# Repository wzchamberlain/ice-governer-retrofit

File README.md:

# ICE-Governor-Retrofit

## Rationale & Goal

The goal of this project is to provide a low cost electronic governor retrofit for small/carburetor engines to replace poor, worn, malfunctioning, or destroyed governors. Typical off-the-shelf variants cost in excess of $100 USD, surpassing the remaining value of the small engine they might be applied to. The target deployment engine this project is built for specifically is a 4000W single phase (true) generator, where the engine must be kept at a steady 3600 RPM or 3000 RPM for 60 Hz or 50 Hz respectively. Provisions should be made in the design to allow for dynamic target speed setting both for fine tuning or for a dynamic governor, such as in a small tractor or ride on lawnmower, perhaps even a gas powertool.

## Pin Count

### Pin Planning
Max IO: 6 pins. One of the potentiometers should be limited to range of 2.5V to HIGH so that I can be used on the RESET line of the ATTiny (GROUND/LOW Pull is reset active).
1. Spark Detect +
    - Bit 2 (Pin7) is the external interrupt pin and would be preferred, however there is only one external interrupt.
2. Spark Detect -
    - Bit 0 (Pin 5) for convince, has Pin Change Interrupt.
3. Servo PWM
    - Bit 4 or Bit 1 should be used for the non-inverted PWM output.
    - Pin 6 or Pin 3.
4. Speed (Position) Potentiometer
    - Potentiometer for speed
    - (Optional) Grounding/High switch to signal off.
        - Cannot be on reset (Bit 5, Pin 1)
5. Integral Potentiometer
6. Derivative Potentiometer

### Signaled Shutoff Plan
This variant of the schematic and pin planning uses the switch (SPDT) to signal the ATTiny to ramp down (and stall) the engine before entering a sleep state. This will result in a parasitic draw when in sleep/off to allow the microcontroller to wake up and for the LDO Voltage Regulator to down-regulate the battery. This is done as a trade off to make operation safer by ensuring that the throttle body is closed to prevent a runaway. The battery planned is a relatively larger 9V box battery.

#### By Pin Number
1. Second Order Reaction
2. First Order Reaction
3. Speed Set and Sleep Trigger
4. GND
5. Spark Trigger
6. Servo Position PWM
7. Spark Trigger
8. VCC

#### By Port Number (All Port B)
0. Spark Trigger
1. Servo Position PWM
2. Spark Trigger
3. First Order Reaction
4. Speed Set and Sleep Trigger
5. Second Order Reaction

#### Schematic Plan

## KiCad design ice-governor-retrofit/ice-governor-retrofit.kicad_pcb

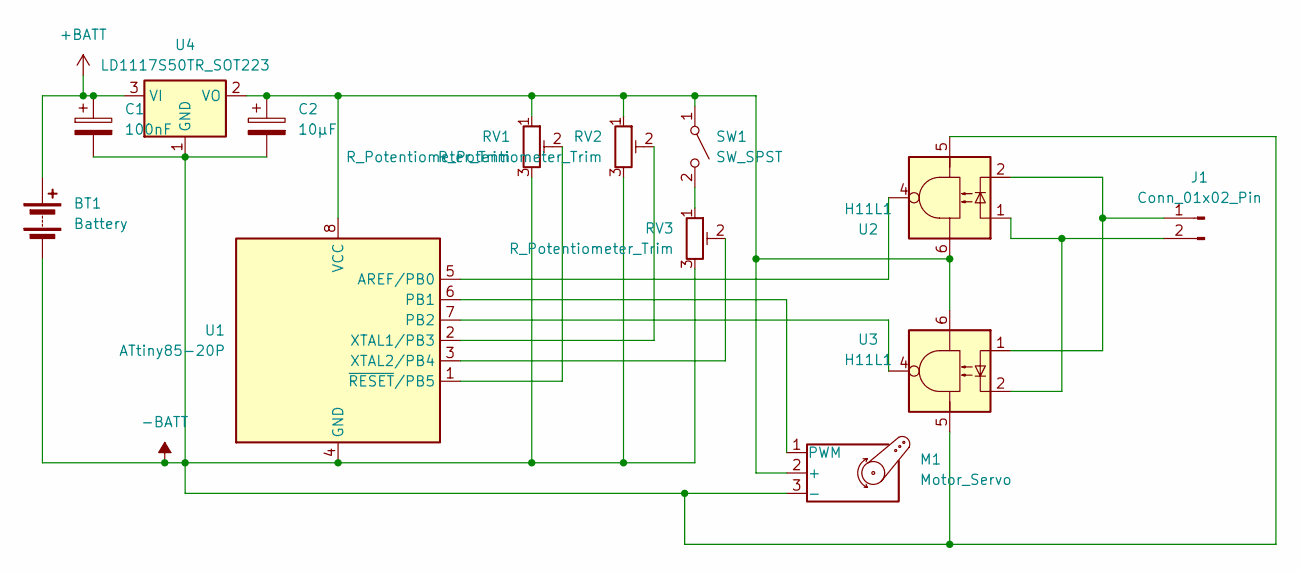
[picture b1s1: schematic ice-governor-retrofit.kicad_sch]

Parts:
BT1: Battery; BatteryHolder_Eagle_12BH611-GR
C1: 100nF; CP_Radial_D5.0mm_P2.50mm
C2: 10μF; CP_Radial_D5.0mm_P2.50mm
J1: Conn_01x02_Pin; PinHeader_1x02_P2.54mm_Vertical
M1: Motor_Servo; PinHeader_1x03_P2.54mm_Vertical
RV1, RV2, RV3: R_Potentiometer_Trim; Potentiometer_Vishay_43_Horizontal
SW1: SW_SPST; PinHeader_1x02_P2.54mm_Vertical
U1: ATtiny85-20P; DIP-8_W7.62mm
U2, U3: H11L1; DIP-6_W7.62mm
U4: LD1117S50TR_SOT223; SOT-223-3_TabPin2

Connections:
+BATT: BT1.1 (+), C1.1, U4.3 (VI)
-BATT: BT1.2 (-), C1.2, C2.2, M1.3 (-), RV1.3, RV2.3, RV3.3, U1.4 (GND), U2.5, U3.5, U4.1 (GND)
unnamed: J1.1, U2.2, U3.1
unnamed: J1.2, U2.1, U3.2
unnamed: C2.1, M1.2 (+), RV1.1, RV2.1, SW1.1 (A), U1.8 (VCC), U2.6, U3.6, U4.2 (VO)
unnamed: M1.1 (PWM), U1.6 (PB1)
unnamed: RV3.1, SW1.2 (B)
unnamed: U1.5 (AREF/PB0), U2.4
unnamed: U1.7 (PB2), U3.4
unnamed: RV2.2, U1.2 (XTAL1/PB3)
unnamed: RV3.2, U1.3 (XTAL2/PB4)
unnamed: RV1.2, U1.1 (~RESET/PB5)

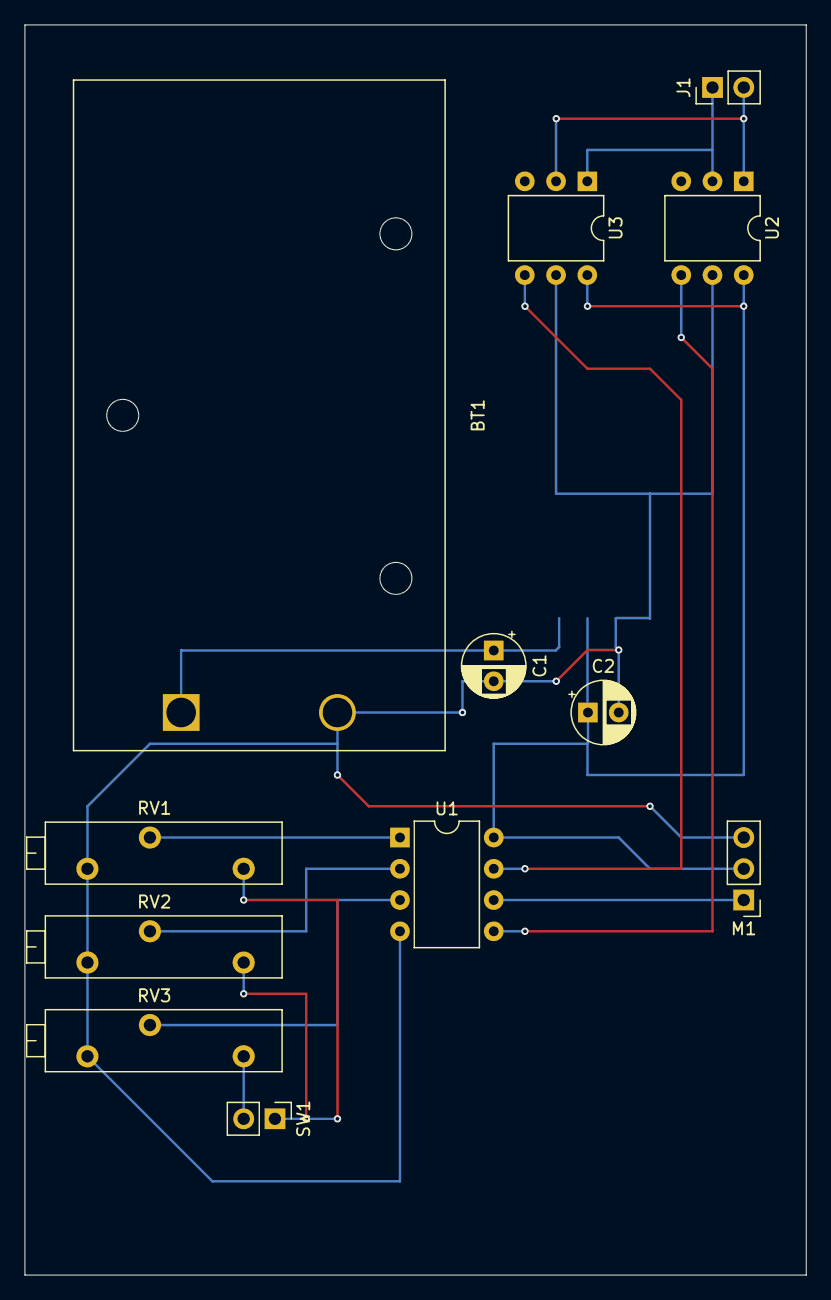
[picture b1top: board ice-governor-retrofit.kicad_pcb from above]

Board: 2 copper layers, 63.5 x 101.6 mm, 13 parts (1 on the bottom side), 12 nets.

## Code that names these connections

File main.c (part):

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#include <stdint.h> // actually comes from avr, is override by compiler
#include <stdbool.h> // these booleans are actually 1 byte blocks

#define SERVO_PIN PB1 // servo PWM output pin
#define SPARK_PIN0 PB0 // (+) polar spark detect pin
#define SPARK_PIN1 PB2 // (-) polar spark detect pin
#define POS_POT_PIN PB4 // position constant trim potentiometer pin
#define INT_POT_PIN PB3 // integral constant trim potentiometer pin
#define DER_POT_PIN PB5 // derivative constant trim potentiometer pin
#define AWAKE_PIN POS_POT_PIN // pin for wake from sleep and send to sleep (alias for position constant trim potentiometer pin)

#define MIN_SERVO 7
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
    // the forever run loop
    while(true) {
        // measure position pot (PB4, ADC2)
        ADMUX &= ~_BV(MUX0);
        ADMUX |= _BV(MUX1);
        ADMUX &= ~_BV(MUX2);
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        loop_until_bit_is_set(ADCSRA, ADIF); // wait for the conversion to finish
        pos_pot_val = ADCH;
        ADCSRA |= _BV(ADIF); // clear the flag
        // measure integral pot (PB3, ACD3)
        ADMUX |= _BV(MUX0);
        ADMUX |= _BV(MUX1);
        ADMUX &= ~_BV(MUX2);
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        loop_until_bit_is_set(ADCSRA, ADIF);
        int_pot_val = ADCH;
        ADCSRA |= _BV(ADSC);
        // measure derivative pot (PB5, ADC0)
        ADMUX &= _BV(MUX0);
        ADMUX &= _BV(MUX1);
        ADMUX &= _BV(MUX2);
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
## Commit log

2025-05-13 Initial Commit for Ice-Governer-Retrofit,
    Old repo had an exposed email somewhere in it that I couldn't get rid of
    despite rebasing, so this is effectively a squash of the last two (and
    only previous) commits.
2025-12-28 Planning,
    - Modified .gitignore to ignore reference documentation and to ignore drawio backup files.
    - Added ice-governor-retrofit-Signaled-Shutoff.drawio.svg as markdown embeddable schematic.
    - Added ice-governor-retrofit.drawio as schematic and diagram document.
    - Modified README.md to plan pin-outs and to embed schematic.
2025-12-28 Corrected LDO Voltage Regulator Filtering Capacitors,
    - Modified ice-governor-retrofit-Signaled-Shutoff.drawio.svg to reflect updated schematic.
    - Modified ice-governor-retrofit.drawio to add additional filtering capacitor and insert capacitor values.
2025-12-29 Reorganized Files and Directories,
    - Modified .gitignore to reflect updated directory organization.
    - Modified README.md to reference updated image path.
    - Moved FreqCalcs.ods to move the design directory,
    - Moved ice-governor-retrofit.drawio to the design directory.
    - Moved ice-governor-retrofit-Signaled-Shutoff.drawio.svg to the design/assets directory.
2026-03-05 Mostly Implemented now (I think)
2026-03-29 Untested MVP of Permanent Setpoint Full PID,
    - Modified main.c to implement PID calculations and dynamic throttle setting.
2026-03-30 Added Perf-Board Layout,
    - Added ice-governor-retrofit KiCad project for schematic and board
    layout(s). Some components subsituted with equivalent footprints.
